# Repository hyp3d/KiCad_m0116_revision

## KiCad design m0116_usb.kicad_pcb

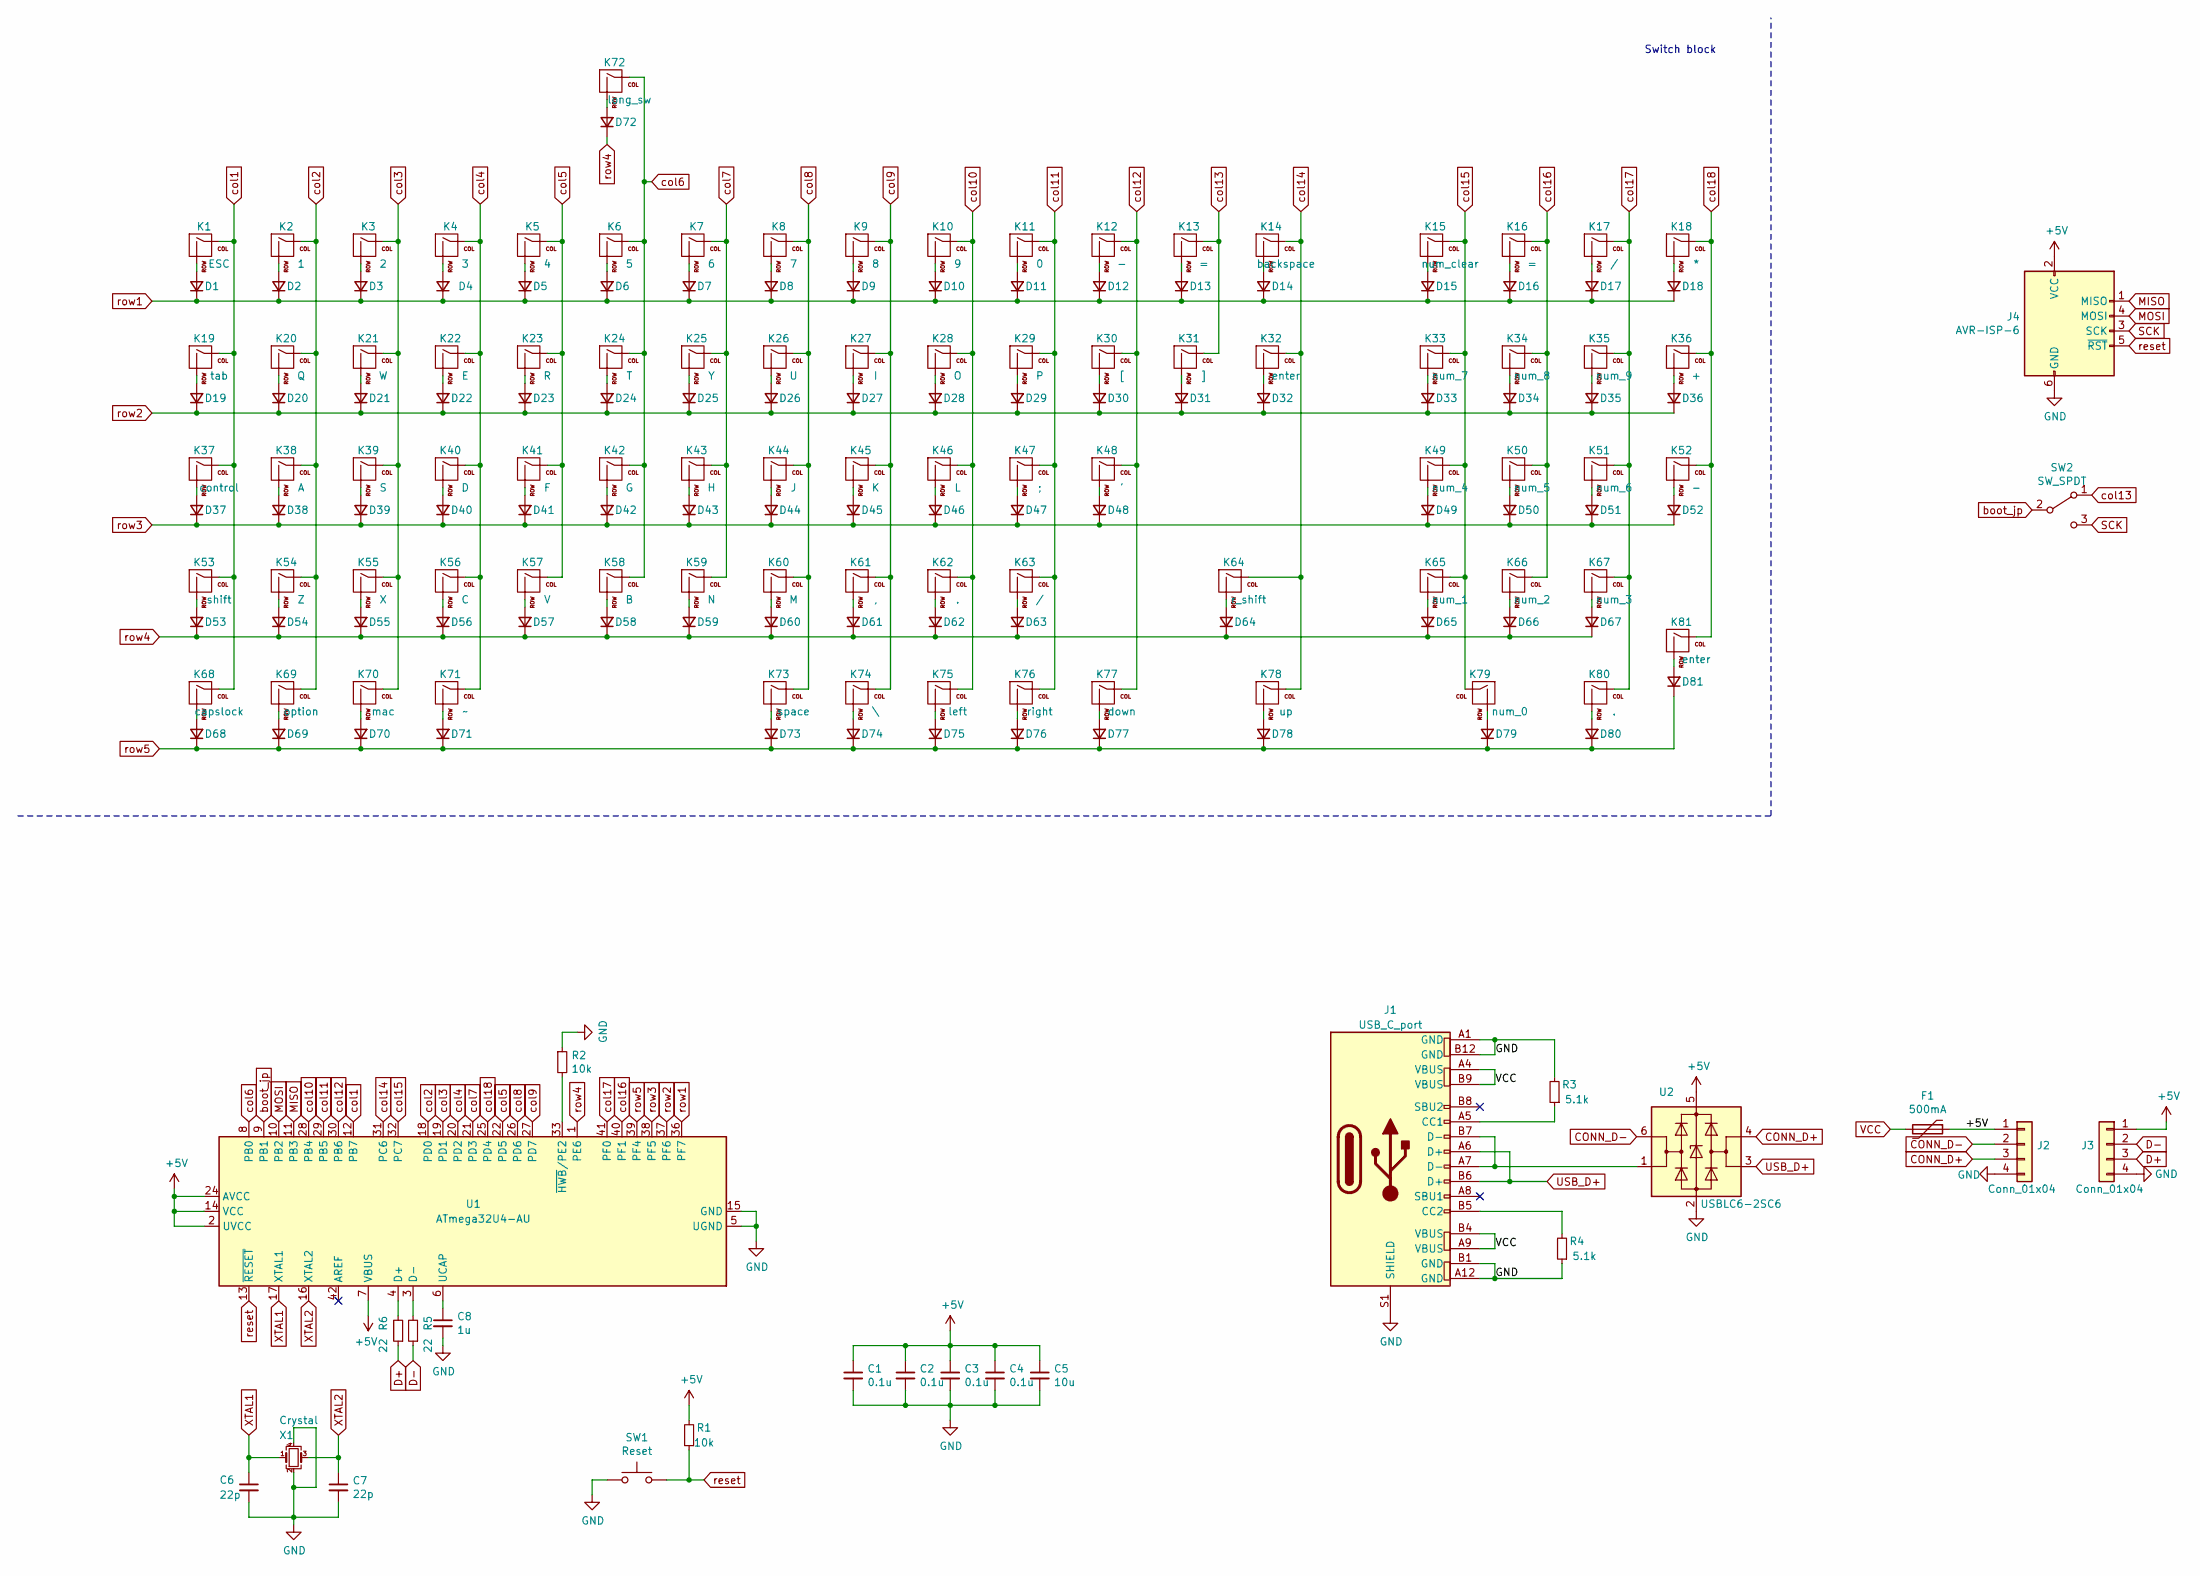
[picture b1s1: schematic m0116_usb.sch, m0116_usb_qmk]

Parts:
C1, C2, C3, C4: 0.1u; C_0603_1608Metric; LCSC Part # C14663
C5: 10u; C_0603_1608Metric; LCSC Part # C19702
C6, C7: 22p; C_0402_1005Metric; LCSC Part # C1555
C8: 1u; C_0402_1005Metric; LCSC Part # C52923
D1, D2, D3, D4, D5, D6, D7, D8, D9, D10, D11, D12, D13, D14, D15, D16, D17, D18, D19, D20, D21, D22, D23, D24, D25, D26, D27, D28, D29, D30, D31, D32, D33, D34, D35, D36, D37, D38, D39, D40, D41, D42, D43, D44, D45, D46, D47, D48, D49, D50, D51, D52, D53, D54, D55, D56, D57, D58, D59, D60, D61, D62, D63, D64, D65, D66, D67, D68, D69, D70, D71, D72, D73, D74, D75, D76, D77, D78, D79, D80, D81: D_Small; D_SOD-123; LCSC Part # C81598
F1: 500mA; Fuse_1206_3216Metric_Castellated; LCSC Part # C135336
J1: USB_C_port; USB_C_Receptacle_XKB_U262-16XN-4BVC11; LCSC Part # C393939
J2: Conn_01x04; PinHeader_1x04_P1.00mm_Vertical
J3: Conn_01x04; PinSocket_1x04_P1.00mm_Vertical_SMD; LCSC Part # C239522
J4: AVR-ISP-6; IDC-Header_2x03_P2.54mm_Vertical
K1: ESC; ALPS-1U
K2: 1; ALPS-1U
K3: 2; ALPS-1U
K4: 3; ALPS-1U
K5: 4; ALPS-1U
K6: 5; ALPS-1U
K7: 6; ALPS-1U
K8: 7; ALPS-1U
K9: 8; ALPS-1U
K10: 9; ALPS-1U
K11: 0; ALPS-1U
K12, K52: -; ALPS-1U
K13, K16: =; ALPS-1U
K14: backspace; ALPS-1U
K15: num_clear; ALPS-1U
K17, K63: /; ALPS-1U
K18: *; ALPS-1U
K19: tab; ALPS-1U
K20: Q; ALPS-1U
K21: W; ALPS-1U
K22: E; ALPS-1U
K23: R; ALPS-1U
K24: T; ALPS-1U
K25: Y; ALPS-1U
K26: U; ALPS-1U
K27: I; ALPS-1U
K28: O; ALPS-1U
K29: P; ALPS-1U
K30: [; ALPS-1U
K31: ]; ALPS-1U
K32, K81: enter; ALPS-1U
K33: num_7; ALPS-1U
K34: num_8; ALPS-1U
K35: num_9; ALPS-1U
K36: +; ALPS-1U
K37: control; ALPS-1U
K38: A; ALPS-1U
K39: S; ALPS-1U
K40: D; ALPS-1U
K41: F; ALPS-1U
K42: G; ALPS-1U
K43: H; ALPS-1U
K44: J; ALPS-1U
K45: K; ALPS-1U
K46: L; ALPS-1U
K47: ;; ALPS-1U
K48: '; ALPS-1U
K49: num_4; ALPS-1U
K50: num_5; ALPS-1U
K51: num_6; ALPS-1U
K53: shift; ALPS-1U
K54: Z; ALPS-1U
K55: X; ALPS-1U
K56: C; ALPS-1U
K57: V; ALPS-1U
K58: B; ALPS-1U
K59: N; ALPS-1U
K60: M; ALPS-1U
K61: ,; ALPS-1U
K62, K80: .; ALPS-1U
K64: r_shift; ALPS-1U
K65: num_1; ALPS-1U
K66: num_2; ALPS-1U
K67: num_3; ALPS-1U
K68: capslock; ALPS-1U
K69: option; ALPS-1U
K70: mac; ALPS-1U
K71: ~~; ALPS-1U
K72: long_sw; ALPS-1U
K73: space; ALPS-1U
K74: \\; ALPS-1U
K75: left; ALPS-1U
K76: right; ALPS-1U
K77: down; ALPS-1U
K78: up; ALPS-1U
K79: num_0; ALPS-1U
R1, R2: 10k; R_0603_1608Metric; LCSC Part # C25197
R3, R4: 5.1k; R_0402_1005Metric; LCSC Part # C23186
R5, R6: 22; R_0603_1608Metric; LCSC Part # C23345
SW1: Reset; SW_SPST_TL3342; LCSC Part # C318884
SW2: SW_SPDT; SW_SPDT_SK-3245S-L1-A; LCSC Part # C405951
U1: ATmega32U4-AU; TQFP-44_10x10mm_P0.8mm; LCSC Part # C44854
U2: USBLC6-2SC6; SOT-23-6; LCSC Part # C2687116
X1: Crystal; Crystal_SMD_3225-4Pin_3.2x2.5mm; LCSC Part # C160456

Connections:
+5V: C1.1, C2.1, C3.1, C4.1, C5.1, F1.1, J2.1, J3.1, J4.2 (VCC), R1.2, U1.2 (UVCC), U1.7 (VBUS), U1.14 (VCC), U1.24 (AVCC), U1.34 (VCC), U1.44 (AVCC), U2.5 (VBUS)
CONN_D+: J2.3, U2.4 (I/O2)
CONN_D-: J2.2, U2.6 (I/O1)
D+: J3.3, R6.1
D-: J3.2, R5.1
GND: C1.2, C2.2, C3.2, C4.2, C5.2, C6.2, C7.2, C8.2, J1.A1 (GND), J1.A12 (GND), J1.B1 (GND), J1.B12 (GND), J1.S1 (SHIELD), J2.4, J3.4, J4.6 (GND), R2.1, R3.2, R4.1, SW1.1, U1.5 (UGND), U1.15 (GND), U1.23 (GND), U1.35 (GND), U1.43 (GND), U2.2 (GND), X1.2, X1.4
MISO: J4.1 (MISO), U1.11 (PB3)
MOSI: J4.4 (MOSI), U1.10 (PB2)
unnamed: C8.1, U1.6 (UCAP)
unnamed: D1.2 (A), K1.2 (ROW)
unnamed: D2.2 (A), K2.2 (ROW)
unnamed: D3.2 (A), K3.2 (ROW)
unnamed: D4.2 (A), K4.2 (ROW)
unnamed: D5.2 (A), K5.2 (ROW)
unnamed: D6.2 (A), K6.2 (ROW)
unnamed: D7.2 (A), K7.2 (ROW)
unnamed: D8.2 (A), K8.2 (ROW)
unnamed: D9.2 (A), K9.2 (ROW)
unnamed: D10.2 (A), K10.2 (ROW)
unnamed: D11.2 (A), K11.2 (ROW)
unnamed: D12.2 (A), K12.2 (ROW)
unnamed: D13.2 (A), K13.2 (ROW)
unnamed: D14.2 (A), K14.2 (ROW)
unnamed: D15.2 (A), K15.2 (ROW)
unnamed: D16.2 (A), K16.2 (ROW)
unnamed: D17.2 (A), K17.2 (ROW)
unnamed: D18.2 (A), K18.2 (ROW)
unnamed: D19.2 (A), K19.2 (ROW)
unnamed: D20.2 (A), K20.2 (ROW)
unnamed: D21.2 (A), K21.2 (ROW)
unnamed: D22.2 (A), K22.2 (ROW)
unnamed: D23.2 (A), K23.2 (ROW)
unnamed: D24.2 (A), K24.2 (ROW)
unnamed: D25.2 (A), K25.2 (ROW)
unnamed: D26.2 (A), K26.2 (ROW)
unnamed: D27.2 (A), K27.2 (ROW)
unnamed: D28.2 (A), K28.2 (ROW)
unnamed: D29.2 (A), K29.2 (ROW)
unnamed: D30.2 (A), K30.2 (ROW)
unnamed: D31.2 (A), K31.2 (ROW)
unnamed: D32.2 (A), K32.2 (ROW)
unnamed: D33.2 (A), K33.2 (ROW)
unnamed: D34.2 (A), K34.2 (ROW)
unnamed: D35.2 (A), K35.2 (ROW)
unnamed: D36.2 (A), K36.2 (ROW)
unnamed: D37.2 (A), K37.2 (ROW)
unnamed: D38.2 (A), K38.2 (ROW)
unnamed: D39.2 (A), K39.2 (ROW)
unnamed: D40.2 (A), K40.2 (ROW)
unnamed: D41.2 (A), K41.2 (ROW)
unnamed: D42.2 (A), K42.2 (ROW)
unnamed: D43.2 (A), K43.2 (ROW)
unnamed: D44.2 (A), K44.2 (ROW)
unnamed: D45.2 (A), K45.2 (ROW)
unnamed: D46.2 (A), K46.2 (ROW)
unnamed: D47.2 (A), K47.2 (ROW)
unnamed: D48.2 (A), K48.2 (ROW)
unnamed: D49.2 (A), K49.2 (ROW)
unnamed: D50.2 (A), K50.2 (ROW)
unnamed: D51.2 (A), K51.2 (ROW)
unnamed: D52.2 (A), K52.2 (ROW)
unnamed: D53.2 (A), K53.2 (ROW)
unnamed: D54.2 (A), K54.2 (ROW)
unnamed: D55.2 (A), K55.2 (ROW)
unnamed: D56.2 (A), K56.2 (ROW)
unnamed: D57.2 (A), K57.2 (ROW)
unnamed: D58.2 (A), K58.2 (ROW)
unnamed: D59.2 (A), K59.2 (ROW)
unnamed: D60.2 (A), K60.2 (ROW)
unnamed: D61.2 (A), K61.2 (ROW)
unnamed: D62.2 (A), K62.2 (ROW)
unnamed: D63.2 (A), K63.2 (ROW)
unnamed: D64.2 (A), K64.2 (ROW)
unnamed: D65.2 (A), K65.2 (ROW)
unnamed: D66.2 (A), K66.2 (ROW)
unnamed: D67.2 (A), K67.2 (ROW)
unnamed: D68.2 (A), K68.2 (ROW)
unnamed: D69.2 (A), K69.2 (ROW)
unnamed: D70.2 (A), K70.2 (ROW)
unnamed: D71.2 (A), K71.2 (ROW)
unnamed: D72.2 (A), K72.2 (ROW)
unnamed: D73.2 (A), K73.2 (ROW)
unnamed: D74.2 (A), K74.2 (ROW)
unnamed: D75.2 (A), K75.2 (ROW)
unnamed: D76.2 (A), K76.2 (ROW)
unnamed: D77.2 (A), K77.2 (ROW)
unnamed: D78.2 (A), K78.2 (ROW)
unnamed: D79.2 (A), K79.2 (ROW)
unnamed: D80.2 (A), K80.2 (ROW)
unnamed: D81.2 (A), K81.2 (ROW)
unnamed: J1.A5 (CC1), R3.1
unnamed: J1.A7 (D-), J1.B7 (D-), U2.1 (I/O1)
unnamed: J1.B5 (CC2), R4.2
unnamed: R2.2, U1.33 (~HWB~/PE2)
unnamed: R5.2, U1.3 (D-)
unnamed: R6.2, U1.4 (D+)
SCK: J4.3 (SCK), SW2.3 (C)
USB_D+: J1.A6 (D+), J1.B6 (D+), U2.3 (I/O2)
VCC: F1.2, J1.A4 (VBUS), J1.A9 (VBUS), J1.B4 (VBUS), J1.B9 (VBUS)
XTAL1: C6.1, U1.17 (XTAL1), X1.1
XTAL2: C7.1, U1.16 (XTAL2), X1.3
boot_jp: SW2.2 (B), U1.9 (PB1)
col1: K1.1 (COL), K19.1 (COL), K37.1 (COL), K53.1 (COL), K68.1 (COL), U1.12 (PB7)
col2: K2.1 (COL), K20.1 (COL), K38.1 (COL), K54.1 (COL), K69.1 (COL), U1.18 (PD0)
col3: K3.1 (COL), K21.1 (COL), K39.1 (COL), K55.1 (COL), K70.1 (COL), U1.19 (PD1)
col4: K4.1 (COL), K22.1 (COL), K40.1 (COL), K56.1 (COL), K71.1 (COL), U1.20 (PD2)
col5: K5.1 (COL), K23.1 (COL), K41.1 (COL), K57.1 (COL), U1.22 (PD5)
col6: K6.1 (COL), K24.1 (COL), K42.1 (COL), K58.1 (COL), K72.1 (COL), U1.8 (PB0)
col7: K7.1 (COL), K25.1 (COL), K43.1 (COL), K59.1 (COL), U1.21 (PD3)
col8: K8.1 (COL), K26.1 (COL), K44.1 (COL), K60.1 (COL), K73.1 (COL), U1.26 (PD6)
col9: K9.1 (COL), K27.1 (COL), K45.1 (COL), K61.1 (COL), K74.1 (COL), U1.27 (PD7)
col10: K10.1 (COL), K28.1 (COL), K46.1 (COL), K62.1 (COL), K75.1 (COL), U1.28 (PB4)
col11: K11.1 (COL), K29.1 (COL), K47.1 (COL), K63.1 (COL), K76.1 (COL), U1.29 (PB5)
col12: K12.1 (COL), K30.1 (COL), K48.1 (COL), K77.1 (COL), U1.30 (PB6)
col13: K13.1 (COL), K31.1 (COL), SW2.1 (A)
col14: K14.1 (COL), K32.1 (COL), K64.1 (COL), K78.1 (COL), U1.31 (PC6)
col15: K15.1 (COL), K33.1 (COL), K49.1 (COL), K65.1 (COL), K79.1 (COL), U1.32 (PC7)
col16: K16.1 (COL), K34.1 (COL), K50.1 (COL), K66.1 (COL), U1.40 (PF1)
col17: K17.1 (COL), K35.1 (COL), K51.1 (COL), K67.1 (COL), K80.1 (COL), U1.41 (PF0)
col18: K18.1 (COL), K36.1 (COL), K52.1 (COL), K81.1 (COL), U1.25 (PD4)
reset: J4.5 (~RST), R1.1, SW1.2, U1.13 (~RESET)
row1: D1.1 (K), D2.1 (K), D3.1 (K), D4.1 (K), D5.1 (K), D6.1 (K), D7.1 (K), D8.1 (K), D9.1 (K), D10.1 (K), D11.1 (K), D12.1 (K), D13.1 (K), D14.1 (K), D15.1 (K), D16.1 (K), D17.1 (K), D18.1 (K), U1.36 (PF7)
row2: D19.1 (K), D20.1 (K), D21.1 (K), D22.1 (K), D23.1 (K), D24.1 (K), D25.1 (K), D26.1 (K), D27.1 (K), D28.1 (K), D29.1 (K), D30.1 (K), D31.1 (K), D32.1 (K), D33.1 (K), D34.1 (K), D35.1 (K), D36.1 (K), U1.37 (PF6)
row3: D37.1 (K), D38.1 (K), D39.1 (K), D40.1 (K), D41.1 (K), D42.1 (K), D43.1 (K), D44.1 (K), D45.1 (K), D46.1 (K), D47.1 (K), D48.1 (K), D49.1 (K), D50.1 (K), D51.1 (K), D52.1 (K), U1.38 (PF5)
row4: D53.1 (K), D54.1 (K), D55.1 (K), D56.1 (K), D57.1 (K), D58.1 (K), D59.1 (K), D60.1 (K), D61.1 (K), D62.1 (K), D63.1 (K), D64.1 (K), D65.1 (K), D66.1 (K), D67.1 (K), D72.1 (K), U1.1 (PE6)
row5: D68.1 (K), D69.1 (K), D70.1 (K), D71.1 (K), D73.1 (K), D74.1 (K), D75.1 (K), D76.1 (K), D77.1 (K), D78.1 (K), D79.1 (K), D80.1 (K), D81.1 (K), U1.39 (PF4)

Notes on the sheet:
Switch block

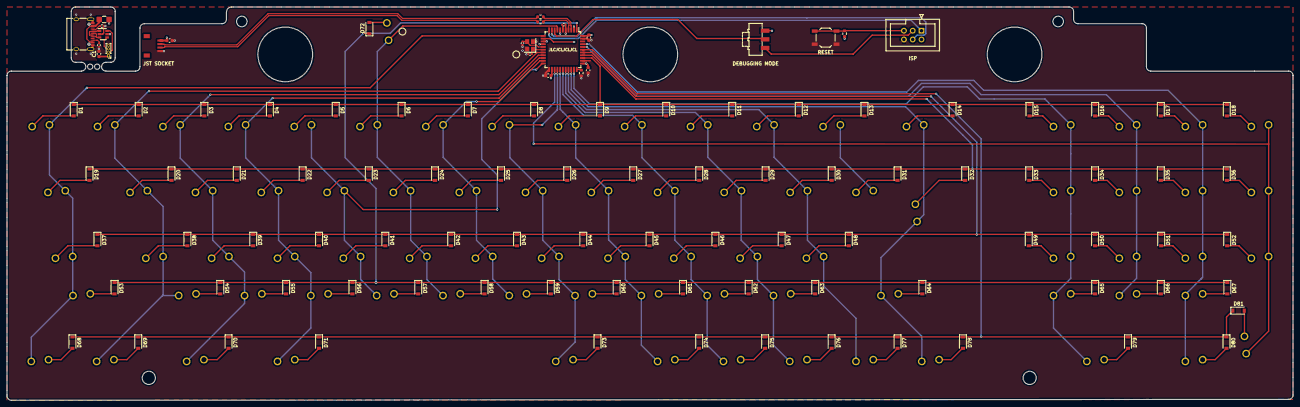
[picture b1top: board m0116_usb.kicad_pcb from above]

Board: 4 copper layers, 372.1 x 113.8 mm, 186 parts (0 on the bottom side), 126 nets.

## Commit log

2021-09-09 clean up the project library
2021-09-09 change ucontroller to ATmega32u4
2021-09-14 populate smd components, routing, finalize rev2
2021-09-20 replace smd jumper with spdt switch
2021-09-29 revise daughterboard, finalize
